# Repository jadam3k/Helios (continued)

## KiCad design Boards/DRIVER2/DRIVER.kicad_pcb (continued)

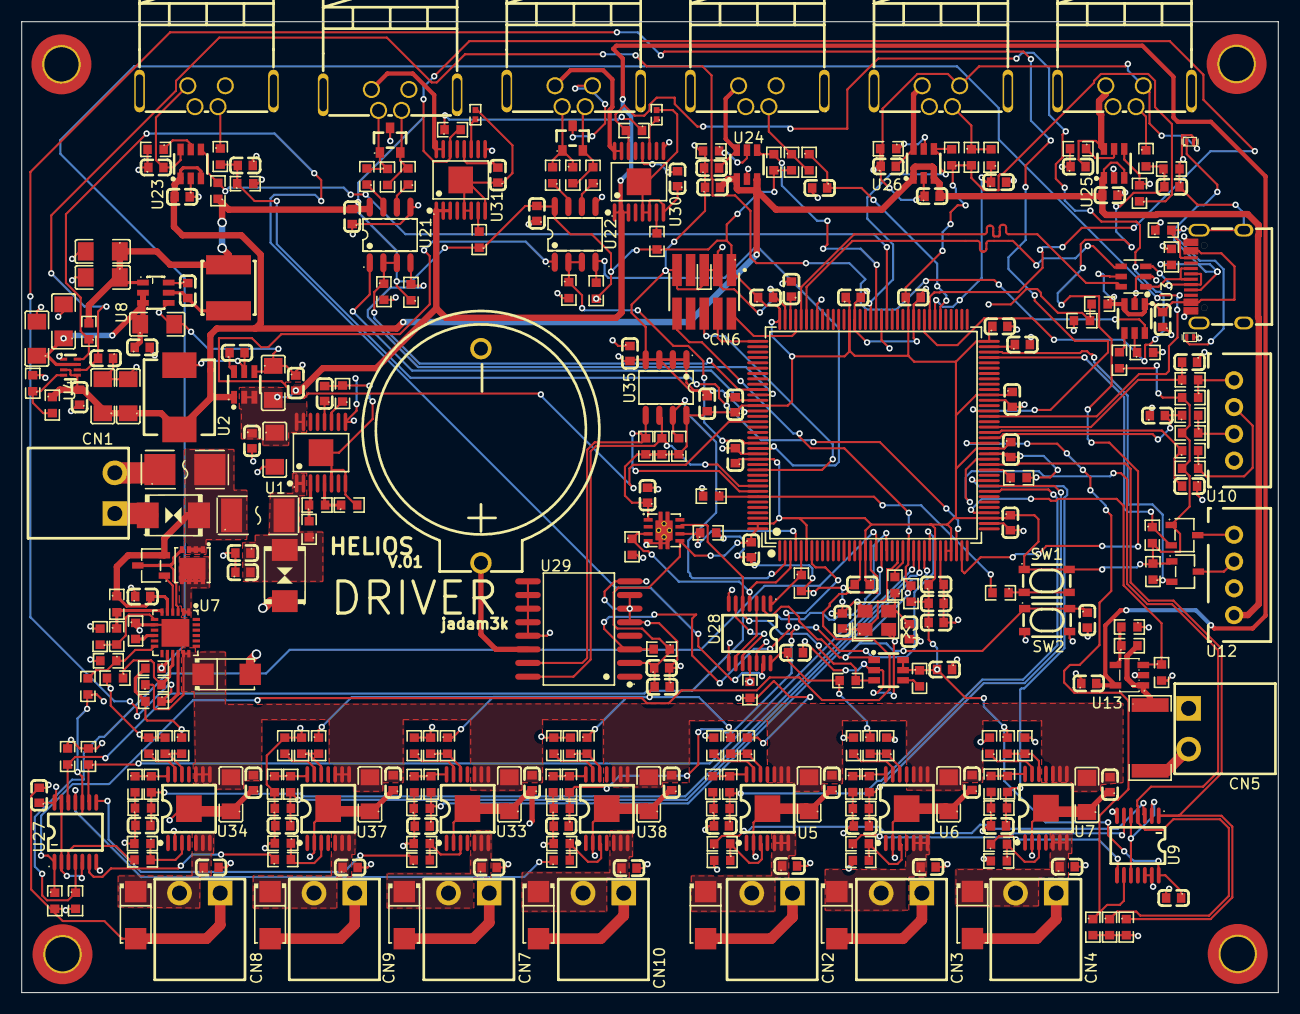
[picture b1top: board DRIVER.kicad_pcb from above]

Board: 4 copper layers, 117.3 x 90.6 mm, 322 parts (0 on the bottom side), 183 nets.

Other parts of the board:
M13, M13#2, M13#3, M13#4: MountingHole_3.2mm_M3_DIN965_Pad_TopBottom

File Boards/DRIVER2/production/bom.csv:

Designator,Footprint,Quantity,Value,LCSC Part #
BT1,C2895401_BAT-TH_BS-2-1,1,BS-2-1,C2895401
"C1, C11, C23, C25, C39, C62, C63, C70, C71, C82, C88",C15849_C0603,11,1uF,C15849
"C10, C12, C13, C2, C20, C24, C27, C31, C33, C34, C36, C37, C38, C40, C41, C42, C43, C44, C45, C46, C47, C48, C5, C53, C55, C57, C58, C59, C60, C65, C66, C67, C68, C69, C72, C73, C74, C75, C76, C79, C8, C80, C81, C87, C89, C9, C92, C93",C14663_C0603,48,100nF,C14663
"C14, C15, C21, C22, C32, C35, C83, C84, C85, C86, C94, C95, C96, C97",C1589_C0603,14,10nF,C1589
"C16, C17, C18, C19, C28, C29",C12891_C1206,6,22uF,C12891
"C26, C3, C30, C4, C6, C7, C77, C78, C90, C91",C13585_C1206,10,10uF,C13585
"C49, C51, C52, C61",C57112_C0603,4,10nF,C57112
"C50, C54",C1607_C0603,2,2.2uF,C1607
"C56, C64",C1647_C0603,2,18pF,C1647
CN1,C507005_CONN-TH_2P-P3_81_JL15EDGRC-38102G01,1,15EDGRC-3.81-02P,C507005
"CN10, CN2, CN3, CN4, CN5, CN7, CN8, CN9",C507005_CONN-TH_2P-P3_81_JL15EDGRC-38102G01,8,15EDGRC-3.81-02P-14-00A(H),C507005
CN6,C448647_CONN-SMD_FTSH-105-01-L-DV-K-TR,1,FTSH-105-01-L-DV-K-TR,C448647
"D1, D2",C83327_SMB_L4_6-W3_6-LS5_3-BI,2,SMBJ18CA,C83327
"D10, D11, D12, D13, D3, D4, D5, D7",C65009_SMA_L4_3-W2_6-LS5_2-RD,8,SS56,C65009
D6,C7519_SOT-23-6_L2_9-W1_6-P0_95-LS2_8-BL,1,USBLC6-2SC6,C7519
"D8, D9",C404012_SOT-23_L2_9-W1_3-P1_90-LS2_4-BR,2,CDSOT23-SM712,C404012
"E1, E2",C84374_SOD-882_L1_0-W0_6-BI,2,14V,C84374
F1,C178980_FUSE-SMD_L6_1-W2_7,1,"8A,65V",C178980
F2,C99547_FUSE-SMD_L6_1-W2_7_0451002_MRL,1,2 A / 0451002.MRL.,C99547
L1,C3040353_IND-SMD_L7_0-W6_6,1,FAUL0630,C3040353
L2,C167962_IND-SMD_L5_0-W5_0_FNR50XXS,1,FNR5040S3R9NT,C167962
Q1,C478469_DFN-8_L3_3-W3_3-P0_65-BL-3,1,CSD19537Q3,C478469
"Q2, Q3, Q4",C40912_SOT-23-3_L2_9-W1_6-P1_90-LS2_8-BR,3,BSS138-7-F,C40912
"R1, R106, R107, R110, R111, R126, R127, R129, R130, R134, R135, R2, R3, R36, R37, R4, R46, R51, R52, R55, R61, R73, R82",C23162_R0603,23,4.7k,C23162
"R10, R102, R103, R104, R105, R117, R119, R12, R120, R121, R122, R123, R128, R140, R141, R142, R143, R15, R17, R18, R19, R25, R27, R28, R33, R41, R42, R48, R49, R50, R57, R59, R62, R63, R64, R65, R66, R74, R75, R80, R81, R83, R84, R86, R87, R89, R90, R95, R96, R97, R98, R99",C25804_R0603,52,10k,C25804
"R100, R101, R23, R93, R94",C25808_R0603,5,120k,C25808
"R108, R109, R11, R112, R113, R131, R132, R133, R136, R137, R34, R35, R38, R39, R5, R6, R7, R8",C25803_R0603,18,100k,C25803
"R114, R116",C2986234_R0402,2,60.4k,C2986234
"R115, R118, R13, R138, R139, R14, R40",C23179_R0603,7,470R,C23179
"R124, R125, R144, R145, R20, R21, R43",C23253_R0603,7,820R,C23253
R16,C22790_R0603,1,12k,C22790
R22,C23231_R0603,1,68k,C23231
R24,C25981_R0603,1,8.2k,C25981
R26,C23040_R0603,1,"4.02 kΩ, ±1%",C23040
"R29, R32",C23240_R0603,2,750k,C23240
R30,C54531393_R0603,1,34.8k,C54531393
R31,C14891_R0603,1,64.9k,C14891
"R44, R45",C23186_R0603,2,5.1k,C23186
"R47, R53, R54, R76, R85, R88",C21190_R0603,6,1KΩ,C21190
R56,C22935_R0603,1,1M,C22935
R58,C31850_R0603,1,22k,C31850
R60,C35218_R2512,1,100R,C35218
R67,C4216_R0603,1,33k,C4216
R68,C23254_R0603,1,82k,C23254
"R69, R70, R71, R72",C313648_R0603,4,10R,C313648
"R77, R78",C22809_R0603,2,15k,C22809
R79,C21189_R0603,1,0R0,C21189
R9,C22984_R0603,1,30k,C22984
"R91, R92",C22787_R0603,2,120R,C22787
"SW1, SW2",C139797_KEY-SMD_4P-L4_2-W3_2-P2_20-LS4_6,2,SKRPACE010,C139797
"U1, U30, U31",C544399_HTSSOP-16_L5_0-W4_4-P0_65-LS6_4-BL-EP2_5,3,TPS26600PWPR,C544399
"U10, U12",C144395_CONN-TH_B4B-XH-A-LF-SN,2,B4B-XH-A(LF)(SN),C144395
"U11, U33, U34, U37, U38, U5, U6",C475505_PDSO-G14_L5_0-W4_4-P0_65-LS6_4-BL-EP,7,TPS1H100BQPWPRQ1,C475505
U13,C221351_SOT-23-5_L3_0-W1_7-P0_95-LS2_8-BR,1,OPA197IDBVR,C221351
U14,C46525_LQFP-144_L20_0-W20_0-P0_50-LS22_0-BL,1,STM32F429ZGT6,C46525
"U15, U16, U17, U18, U19, U20",C19108970_SMA-TH_M8-S4A-GPL-M10-JD,6,M8-S4A-GPL M10-JD,C19108970
U2,C2071056_TSOT-23-6_L2_9-W1_6-P0_95-LS2_8-BL,1,AP63205WU-7,C2071056
"U21, U22",C2671345_SOIC-8_L4_9-W3_9-P1_27-LS6_0-BL,2,THVD1410DR,C2671345
"U23, U24, U25, U26, U3",C55266_SOT-23-6_L2_9-W1_6-P0_95-LS2_8-BR,5,TPS2553DBVR,C55266
"U27, U28, U9",C2867158_TSSOP-14_L4_9-W4_4-P0_65-LS6_4-BL,3,SN74HCS08QPWRQ1,C2867158
U29,C9866_SOIC-16_L10_3-W7_5-P1_27-LS10_3-BL,1,DS3231,C9866
U32,C702145_VSON-8_L3_0-W3_0-P0_65-TL-EP,1,TPS3431SDRBR,C702145
U35,C66020_SOIC-8_L4_9-W3_9-P1_27-LS6_0-BL,1,FM24W256-GTR,C66020
U36,C43698_SOT-23-6_L2_9-W1_6-P0_95-LS2_8-BR,1,TPS3808G33DBVR,C43698
U4,C3235557_SOT-583-8_L2_1-W1_6-P0_50-LS1_6-BL,1,TPS2116DRLR,C3235557
U7,C1850273_VQFN-24_L4_0-W4_0-P0_50-BL-EP2_5,1,TPS26631RGER,C1850273
U8,C780769_TSOT-26_L2_9-W1_6-P0_95-LS2_8-BL,1,AP63203WU-7,C780769
USBC1,C165948_USB-C_SMD-TYPE-C-31-M-12_1,1,TYPE-C-31-M-12,C165948
X1,C2682775_CRYSTAL-SMD_4P-L3_2-W2_5-BL,1,X32258MOB4SI,C2682775

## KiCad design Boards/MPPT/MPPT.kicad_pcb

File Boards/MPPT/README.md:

# Helios MPPT

Solar power board for the Helios greenhouse controller, using an STM32L072CZT6. The original schematic and PCB are preserved. The 8P8C connector is not used by the firmware.

[PCB view](media/helios-mppt-pcb.png) · [Board video](media/helios-mppt-preview.mp4) · [Schematic](docs/MPPT.pdf) · [STEP](docs/MPPT.step) · [Interactive BOM](bom/ibom.html)

## Current firmware

The complete firmware now includes actual power-stage PWM, voltage/current/temperature measurements, current and voltage limiting, output-power perturb-and-observe, Li-ion charge termination/restart, load hysteresis, latched faults, a control heartbeat and watchdog.

[Open the Arduino sketch](firmware/HeliosMPPT/HeliosMPPT.ino) · [All source files in one text source text](firmware/COMPLETE_SOURCE.txt) · [Full firmware ZIP](firmware/HeliosMPPT-full.zip) · [Setup and calibration](firmware/README.md) · [Build results](firmware/BUILD_RESULTS.txt)

Compiled successfully for Generic L072CZTx with STM32 Arduino core 3.1.0, in both the default and confirmed charging configurations, with no compiler warnings. Host tests passed 25 checks and exercised 88 duty settings in both timer directions. The assembled board and charger still need bench testing.

**Battery/calibration confirmation defaults to off.** After confirming a protected 3S Li-ion battery and calibrating sensors, set HELIOS_BATTERY_CONFIRMED and HELIOS_CALIBRATION_CONFIRMED to 1 in Config.h. The implemented charger then starts automatically after valid solar qualification. This is a 12.55 V / 2 A reference profile; it is not for AGM or 4S LiFePO4. TH1 beta remains an explicit calibration input.

The original AP2210 and LM5109B supply operating limits remain relevant. A 14.5 V AGM profile is not supported by the unchanged design. Default diode freewheeling raises low-side losses; the optional synchronous mode and actual MOSFET waveforms require bench checks. See the firmware instructions for the controls and limits.

## Hardware

| Block | Components | Purpose |
| --- | --- | --- |
| MCU | STM32L072CZTx, LQFP48 | ADC, DAC, GPIO and timer control; supported by the STM32 Arduino core |
| Converter | Q3–Q5 PSMN5R2-60YL, LM5109BMA, L1 CPEX3222L-470MC-RS | Solar input switching and synchronous buck stage |
| Current sensing | INA2181A1, two 3 mΩ shunts | Converter output current and load current; nominal sensitivity 60 mV/A |
| Voltage sensing | 100 kΩ / 5.6 kΩ dividers | Battery and solar voltage; divider ratio 18.857 |
| Temperature | TH1 10 kΩ NTC | Temperature input; its beta value is not specified in the design |
| Load switch | BSC084P03NS3 G, MMBT3904 | MCU-controlled battery/load output |
| Auxiliary power | LMR33630, AP2210K-3.3 | 5 V buck and 3.3 V LDO |
| Connections | Three screw terminals, XT30, two USB-A sockets, SWD | Power, loads and programming |

The XT30 output is on the unswitched load rail. Turning off LOAD_EN does not disconnect it or the 5 V buck. F2 is a fuse holder: the fitted fuse must be specified separately. Component headline current ratings do not establish the assembled board's continuous current rating.

## Connector and firmware pin map

| Connection | MCU / connector assignment |
| --- | --- |
| Solar U1 | Pin 2 SOLAR+, pin 1 SOLAR−; use the labeled input return |
| Battery U6 | Pin 1 BAT+, pin 2 GND |
| Switched load U5 | Pin 1 switched positive, pin 2 GND |
| XT30 U4 | Pin 1 LOAD_SOLAR, pin 2 GND |
| SWD J4 | 1 VTref 3.3 V, 2 SWCLK, 3 GND, 4 SWDIO, 5 NRST |
| Battery / panel voltage | PA0 / PA1 |
| Current reference DAC | PA4; approximately half VDDA |
| Load / converter current | PA5 / PA6 |
| NTC measurement / return | PA7 / PA8 |
| Driver HI / LI | PB0 / PB1; TIM3 CH3/CH4 PWM, LOW while stopped or unconfigured |
| Switched load enable | PC13; active-HIGH switched load with voltage hysteresis and fault shutdown |
| PV measurement enable | PC14; HIGH enables the divider, not the power converter |
| 5 V status | PC15; Q8 makes LOW mean power-good |
| 5 V buck enable | PB10 |

## Getting started

Open the Arduino sketch using [these firmware instructions](firmware/README.md). For the connections between both boards and the first hardware checks, see [system setup](../../docs/SETUP.md). The defaults leave charging off until the battery and calibration settings are confirmed.

## Project files

| Path | Contents |
| --- | --- |
| `MPPT.kicad_pro`, `.kicad_sch`, `.kicad_pcb` | Original KiCad project and source files |
| `libs/`, `fp-lib-table`, `sym-lib-table` | Required local symbols, footprints and models |
| `firmware/HeliosMPPT/` | Complete Arduino sketch, configuration, controller and PWM driver |
| `firmware/tests/` | Host C++ controller tests |
| `docs/` | Schematic PDF and STEP model |
| `media/` | Render, PCB image and original video |
| `MPPT.glb` | Interactive 3D model, kept beside the KiCad project export settings |
| `production/` | Existing manufacturing exports, preserved unchanged |
| `bom/` | Interactive BOM and a source-derived parts list with available links |

## Bill of materials

[Original manufacturing BOM](production/bom.csv) · [Expanded parts list](bom/parts-with-links.csv) · [Combined system BOM](../../BOM.csv)

The table describes the original board. Parts without an assigned supplier number still need an exact manufacturer part to be selected, including the necessary voltage, power and package ratings.

The tables use direct supplier product links. Prices are USD per component at the stated quantity tier, checked on **November 19, 2026**. Costs use the required component quantities; the final cart can cost more because of minimum order quantities. Shipping, tax, fabrication and assembly are separate.

| References | Qty | Board value | Manufacturer part | Supplier | USD/part | Price tier |
| --- | ---: | --- | --- | --- | ---: | ---: |
| C1 | 1 | 10nF | — | Not selected | — | — |
| C2, C21, C36 | 3 | 2.2uF | — | Not selected | — | — |
| C3, C6, C8, C26, C27, C28, C29, C30, C31, C34 | 10 | 100nF | — | Not selected | — | — |
| C4 | 1 | 1200uF | — | Not selected | — | — |
| C5, C10, C12, C15, C16, C17, C18, C20, C23, C38 | 10 | 10nF | — | Not selected | — | — |
| C7 | 1 | 4.7uF | — | Not selected | — | — |
| C9, C11, C13 | 3 | 1nF | — | Not selected | — | — |
| C14 | 1 | 820uF | — | Not selected | — | — |
| C19 | 1 | 1uF | — | Not selected | — | — |
| C22 | 1 | 150uF | — | Not selected | — | — |
| C24 | 1 | 10uF | — | Not selected | — | — |
| C25 | 1 | 220nF | — | Not selected | — | — |
| C32, C41 | 2 | 2.2uF | — | Not selected | — | — |
| C33, C35, C37, C39 | 4 | 22uF | — | Not selected | — | — |
| C40 | 1 | 100pF | — | Not selected | — | — |
| D1, D2, D5 | 3 | 1N4148W | — | Not selected | — | — |
| D3 | 1 | SS14 | — | Not selected | — | — |
| D4 | 1 | SMBJ24A_C123819 | SMBJ24A | [C123819](https://www.lcsc.com/product-detail/C123819.html) | 0.0593 | 10 |
| F2 | 1 | 3557-2 | 3557-2 | [C352820](https://www.lcsc.com/product-detail/C352820.html) | 1.4802 | 1 |
| J4 | 1 | Conn_01x05 | — | Not selected | — | — |
| L1 | 1 | CPEX3222L-470MC-RS | CPEX3222L-470MC-RS | [C53145486](https://www.lcsc.com/product-detail/C53145486.html) | 5.0594 | 1 |
| L2 | 1 | 2.2uH | — | Not selected | — | — |
| L3 | 1 | SRN8040TA | SRN8040TA-100M | [C2044906](https://www.lcsc.com/product-detail/C2044906.html) | 0.7615 | 1 |
| Q2, Q8, Q9 | 3 | BSS83P | — | Not selected | — | — |
| Q3, Q4, Q5 | 3 | PSMN5R2-60YL | — | Not selected | — | — |
| Q6, Q7 | 2 | MMBT3904 | — | Not selected | — | — |
| Q10 | 1 | BSC084P03NS3 G | BSC084P03NS3GATMA1 | [C672354](https://www.lcsc.com/product-detail/C672354.html) | 1.1136 | 1 |
| R1, R17, R18, R25 | 4 | 10k | — | Not selected | — | — |
| R2, R24 | 2 | 24.9k | — | Not selected | — | — |
| R3, R4, R10, R21, R22, R23, R30 | 7 | 100k | — | Not selected | — | — |
| R5, R11 | 2 | 5.6k | — | Not selected | — | — |
| R6 | 1 | 1M | — | Not selected | — | — |
| R7, R9, R27, R29 | 4 | 470 | — | Not selected | — | — |
| R8, R13 | 2 | 4R7 | — | Not selected | — | — |
| R12 | 1 | 4R7 | — | Not selected | — | — |
| R14, R19 | 2 | 3mR | CRE2512-FZ-R001E-3 | [C840615](https://www.lcsc.com/product-detail/C840615.html) | 0.4295 | 1 |
| R15, R26, R28, R31 | 4 | 2.2k | — | Not selected | — | — |
| R16 | 1 | 2R2 | — | Not selected | — | — |
| R20 | 1 | 100 | — | Not selected | — | — |
| RJ1 | 1 | HX-RJ45 90 5631-1X1 8P8C S | HX-RJ45 90 5631-1x1 8P8C S | [C25168872](https://www.lcsc.com/product-detail/C25168872.html) | 0.1430 | 5 |
| TH1 | 1 | 10K NTC | — | Not selected | — | — |
| TP1 | 1 | PWM_HS_TP | — | Not selected | — | — |
| TP2 | 1 | PWM_LS_TP | — | Not selected | — | — |
| TP3 | 1 | REF_TP | — | Not selected | — | — |
| TP4 | 1 | DCDC_CURRENT_TP | — | Not selected | — | — |
| TP5 | 1 | LOAD_CURRENT_TP | — | Not selected | — | — |
| TP6 | 1 | 12VTP | — | Not selected | — | — |
| TP7 | 1 | 5V_TP | — | Not selected | — | — |
| TP8 | 1 | 3.3V_TP | — | Not selected | — | — |
| U1, U5, U6 | 3 | KF135T-10.16-2P | KF135T-10.16-2P | [C475108](https://www.lcsc.com/product-detail/C475108.html) | 0.5699 | 1 |
| U2 | 1 | INA2181A | INA2181A1IDGSR | [C1848164](https://www.lcsc.com/product-detail/C1848164.html) | 0.5701 | 1 |
| U3 | 1 | LM5109BMA | LM5109BMA/NOPB | [C1549317](https://www.lcsc.com/product-detail/C1549317.html) | 1.0736 | 1 |
| U4 | 1 | XT30AW-M.G.Y | XT30AW-M.G.Y | [C19268026](https://www.lcsc.com/product-detail/C19268026.html) | 0.4097 | 1 |
| U7 | 1 | STM32L072CZTx | STM32L072CZT6 | [C1337587](https://www.lcsc.com/product-detail/C1337587.html) | 5.9667 | 1 |
| U8 | 1 | LMR33630 | LMR33630ADDA | [C2866787](https://www.lcsc.com/product-detail/C2866787.html) | 1.0284 | 1 |
| U9 | 1 | AP2210K-3.3TRG1 | AP2210K-3.3TRG1 | [C176959](https://www.lcsc.com/product-detail/C176959.html) | 0.1626 | 5 |
| USB1, USB2 | 2 | USB-231-ARY | USB-231-ARY | [C720525](https://www.lcsc.com/product-detail/C720525.html) | 0.1971 | 5 |

U3, U7 and U8 use catalog references added to the documentation; they do not change the schematic or manufacturing files. Codes recovered from footprint names still need a part/package check before an order.

## Development and reuse

This is part of my Helios greenhouse project. See [development credits](../../CREDITS.md) for assistance and third-party dependencies. A project-wide license has not been selected.

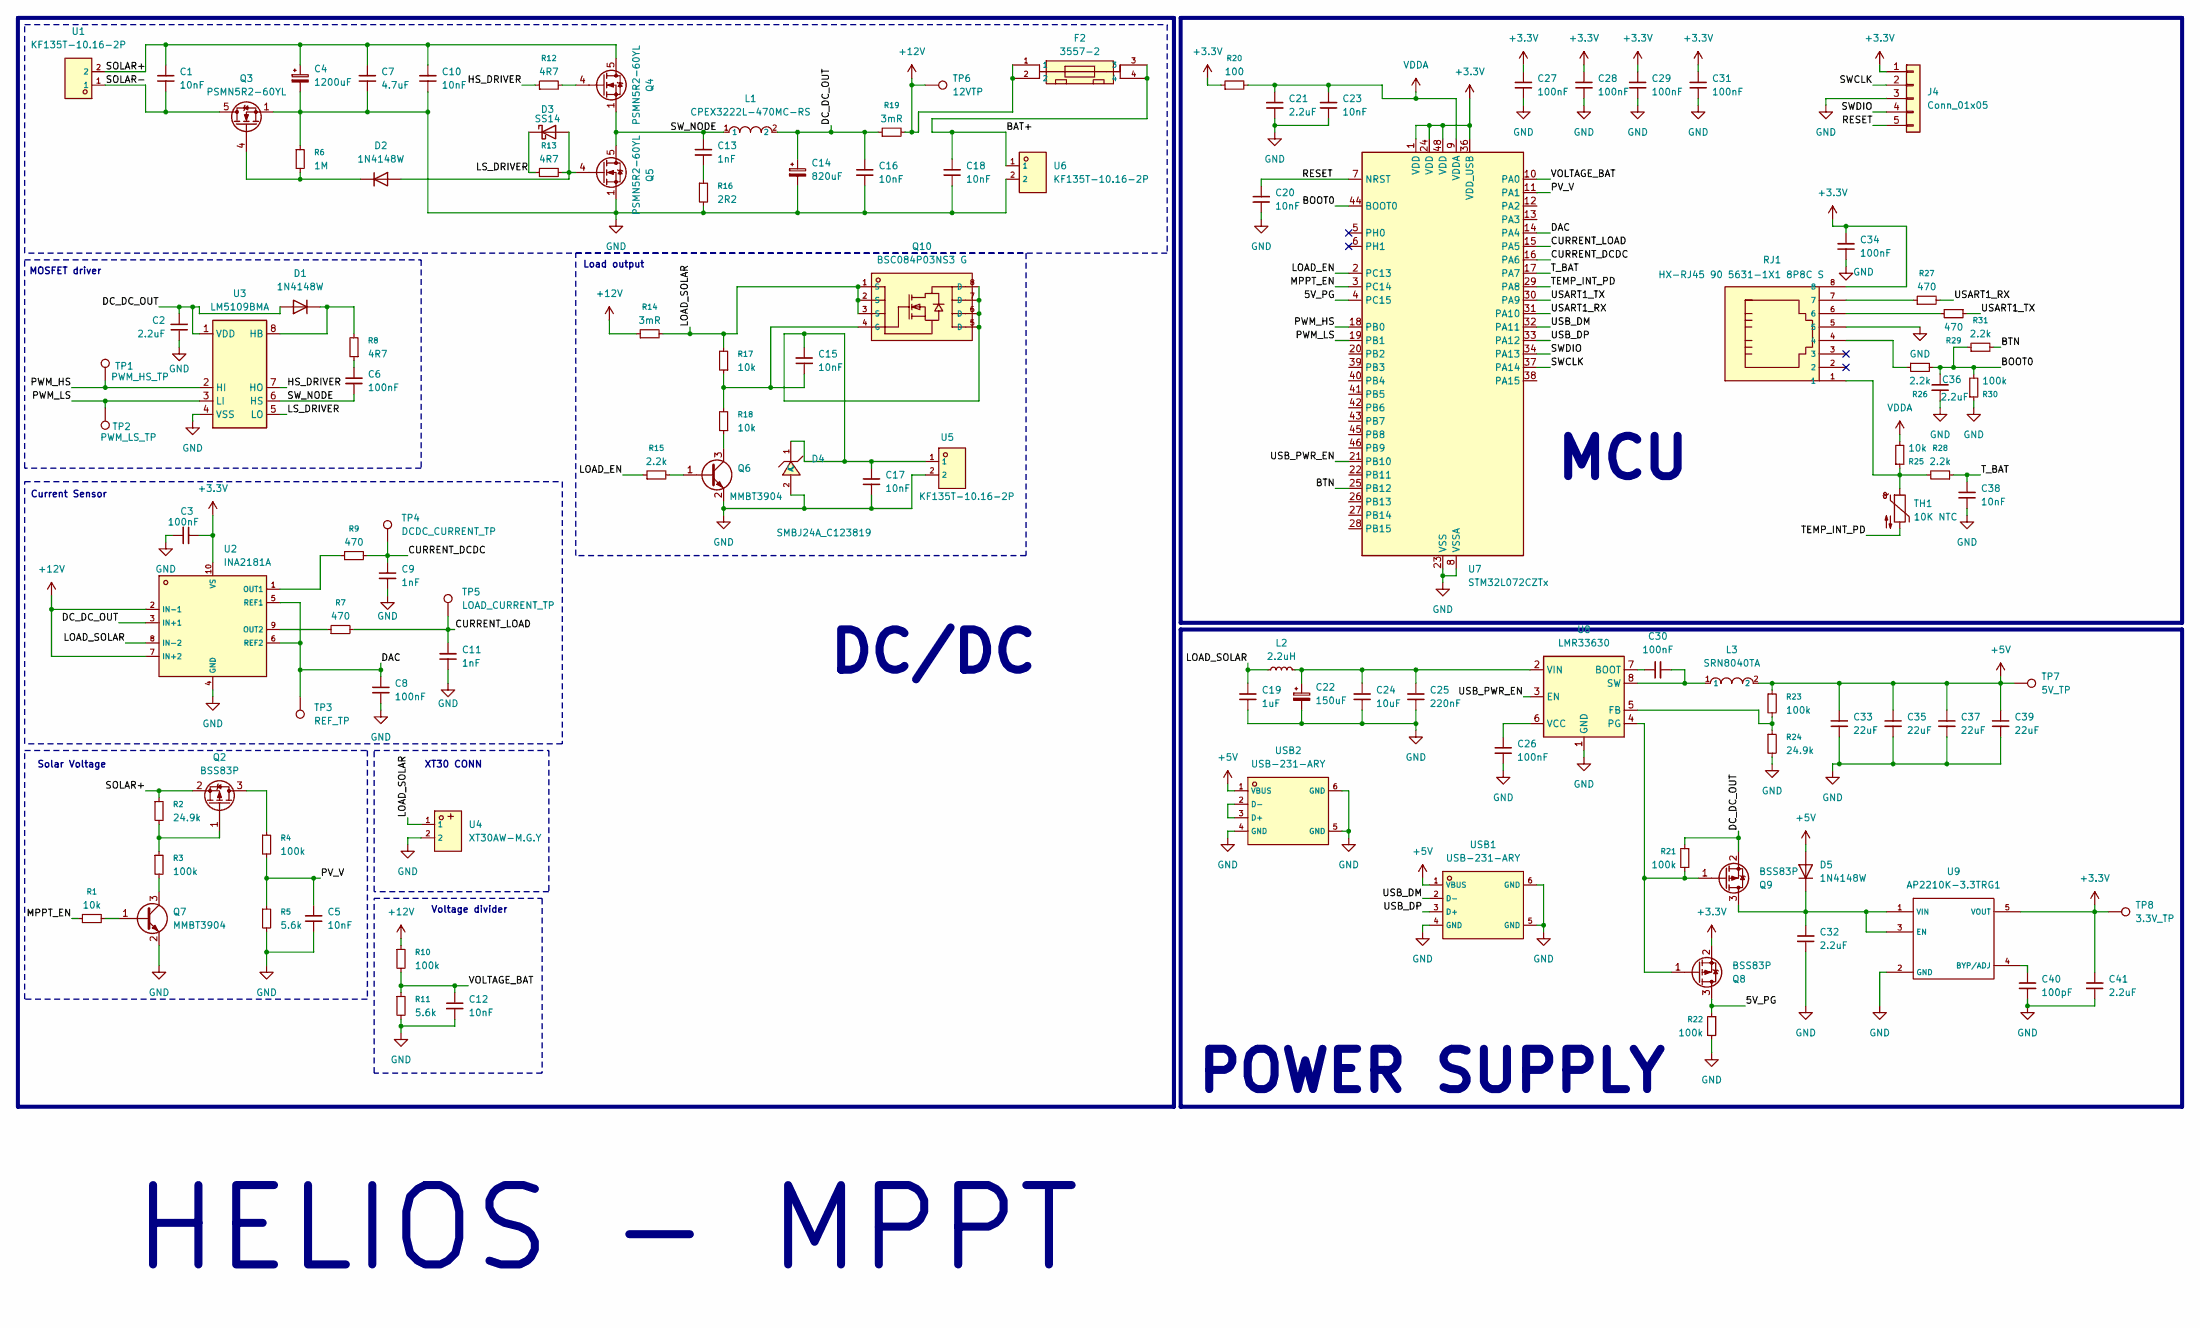
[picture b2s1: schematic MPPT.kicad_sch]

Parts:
C1: 10nF; C_1206_3216Metric
C2, C21, C36: 2.2uF; C_0603_1608Metric
C3, C6, C8, C26, C27, C28, C29, C30, C31, C34: 100nF; C_0603_1608Metric
C4: 1200uF; CP_Radial_D16.0mm_P7.50mm
C5, C10, C12, C15, C16, C17, C18, C20, C23, C38: 10nF; C_0603_1608Metric
C7: 4.7uF; C_1206_3216Metric
C9, C11, C13: 1nF; C_0603_1608Metric
C14: 820uF; CP_Radial_D10.0mm_P5.00mm
C19: 1uF; C_0805_2012Metric
C22: 150uF; CP_Elec_8x6.2
C24: 10uF; C_1210_3225Metric
C25: 220nF; C_0603_1608Metric
C32, C41: 2.2uF; C_1206_3216Metric
C33, C35, C37, C39: 22uF; C_1206_3216Metric
C40: 100pF; C_0603_1608Metric
D1, D2, D5: 1N4148W; D_SOD-123
D3: SS14; D_SMA
D4: SMBJ24A_C123819; C123819_SMB_L4_6-W3_6-LS5_3-RD; LCSC C123819
F2: 3557-2; C352820_FUSE-TH_4P-L19_8-W6_7_3557-2; LCSC C352820
J4: Conn_01x05; PinHeader_1x05_P2.54mm_Vertical
L1: CPEX3222L-470MC-RS; C53145486_IND-TH_L32_2-W22_2_CPEX3222L; LCSC C53145486
L2: 2.2uH; L_Bourns-SRN4018
L3: SRN8040TA; C2044906_IND-SMD_L8_0-W8_0; LCSC C2044906
Q2, Q8, Q9: BSS83P; SOT-23
Q3, Q4, Q5: PSMN5R2-60YL; LFPAK56
Q6, Q7: MMBT3904; SOT-23
Q10: BSC084P03NS3 G; C534379_TDSON-8_L5_2-W5_9-P1_27-LS6_0-BL-EP; LCSC C534379
R1, R17, R18, R25: 10k; R_0603_1608Metric
R2, R24: 24.9k; R_0603_1608Metric
R3, R4, R10, R21, R22, R23, R30: 100k; R_0603_1608Metric
R5, R11: 5.6k; R_0603_1608Metric
R6: 1M; R_0603_1608Metric
R7, R9, R27, R29: 470; R_0603_1608Metric
R8, R13: 4R7; R_0603_1608Metric
R12: 4R7; R_0805_2012Metric
R14, R19: 3mR; C840615_R2512
R15, R26, R28, R31: 2.2k; R_0603_1608Metric
R16: 2R2; R_0603_1608Metric
R20: 100; R_0603_1608Metric
RJ1: HX-RJ45 90 5631-1X1 8P8C S; C25168872_RJ45-TH_HX-RJ45-90; LCSC C25168872
TH1: 10K NTC; R_Axial_DIN0204_L3.6mm_D1.6mm_P5.08mm_Horizontal
TP1: PWM_HS_TP; TestPoint_Pad_D1.0mm
TP2: PWM_LS_TP; TestPoint_Pad_D1.0mm
TP3: REF_TP; TestPoint_Pad_D1.0mm
TP4: DCDC_CURRENT_TP; TestPoint_Pad_D1.0mm
TP5: LOAD_CURRENT_TP; TestPoint_Pad_D1.0mm
TP6: 12VTP; TestPoint_Pad_D1.0mm
TP7: 5V_TP; TestPoint_Pad_D1.0mm
TP8: 3.3V_TP; TestPoint_Pad_D1.0mm
U1, U5, U6: KF135T-10.16-2P; C475108_CONN-TH_P10_16_KF135T-10_16-2P; LCSC C475108
U2: INA2181A; C1848164_VSSOP-10_L3_0-W3_0-P0_50-LS4_9-BL; LCSC C1848164
U3: LM5109BMA; SOIC-8_3.9x4.9mm_P1.27mm
U4: XT30AW-M.G.Y; C19268026_CONN-TH_XT30AW-M_G_Y; LCSC C19268026
U7: STM32L072CZTx; LQFP-48_7x7mm_P0.5mm
U8: LMR33630; Texas_HSOP-8-1EP_3.9x4.9mm_P1.27mm_ThermalVias
U9: AP2210K-3.3TRG1; C176959_SOT-23-5_L3_0-W1_7-P0_95-LS2_8-BR; LCSC C176959
USB1, USB2: USB-231-ARY; C720525_USB-A-TH_USB-231-ARY; LCSC C720525

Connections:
+3.3V: C3.2, C27.1, C28.1, C29.1, C31.1, C34.1, C41.1, J4.1, Q8.2 (S), R20.1, RJ1.8, TP8.1 (1_1), U2.10 (VS), U7.1 (VDD), U7.24 (VDD), U7.36 (VDD_USB), U7.48 (VDD), U9.5 (VOUT)
+5V: C33.1, C35.1, C37.1, C39.1, D5.2 (A), L3.2, R23.1, TP7.1 (1_1), USB1.1 (VBUS), USB2.1 (VBUS)
+12V: F2.1, F2.2, R10.1, R14.1, R19.2, TP6.1 (1_1), U2.2 (IN-1), U2.7 (IN+2)
/5V_PG: Q8.3 (D), R22.1, U7.4 (PC15)
/BAT+: C18.1, F2.3, F2.4, U6.1
/BOOT0: C36.1, R26.2, R30.2, R31.1, U7.44 (BOOT0)
/BTN: R31.2, U7.25 (PB12)
/CURRENT_DCDC: C9.1, R9.2, TP4.1 (1_1), U7.16 (PA6)
/CURRENT_LOAD: C11.1, R7.2, TP5.1 (1_1), U7.15 (PA5)
/DAC: C8.1, TP3.1 (1_1), U2.5 (REF1), U2.6 (REF2), U7.14 (PA4)
/DC_DC_OUT: C2.1, C14.1, C16.1, D1.2 (A), L1.2, Q9.2 (S), R19.1, R21.1, U2.3 (IN+1), U3.1 (VDD)
/HS_DRIVER: R12.1, U3.7 (HO)
/LOAD_EN: R15.1, U7.2 (PC13)
/LOAD_SOLAR: C19.1, L2.1, Q10.1 (S), Q10.2 (S), Q10.3 (S), R14.2, R17.2, U2.8 (IN-2), U4.1
/LS_DRIVER: D3.1 (K), R13.1, U3.5 (LO)
/MPPT_EN: R1.1, U7.3 (PC14)
/PV_V: C5.1, R4.2, R5.1, U7.11 (PA1)
/PWM_HS: TP1.1 (1_1), U3.2 (HI), U7.18 (PB0)
/PWM_LS: TP2.1 (1_1), U3.3 (LI), U7.19 (PB1)
/RESET: C20.1, J4.5, U7.7 (NRST)
/SOLAR+: C1.1, C4.1, C7.1, C10.1, Q2.2 (S), Q4.5 (D), R2.1, U1.2
/SOLAR-: C1.2, Q3.5 (D), U1.1
/SWCLK: J4.2, U7.37 (PA14)
/SWDIO: J4.4, U7.34 (PA13)
/SW_NODE: C6.2, C13.1, L1.1, Q4.1 (S), Q4.2 (S), Q4.3 (S), Q5.5 (D), U3.6 (HS)
/TEMP_INT_PD: TH1.2, U7.29 (PA8)
/T_BAT: C38.1, R28.1, U7.17 (PA7)
/USART1_RX: R27.2, U7.31 (PA10)
/USART1_TX: R29.1, U7.30 (PA9)
/USB_DM: U7.32 (PA11), USB1.2 (D-)
/USB_DP: U7.33 (PA12), USB1.3 (D+)
/USB_PWR_EN: U7.21 (PB10), U8.3 (EN)
/VOLTAGE_BAT: C12.1, R10.2, R11.1, U7.10 (PA0)
GND: C2.2, C3.1, C4.2, C5.2, C7.2, C8.2, C9.2, C10.2, C11.2, C12.2, C14.2, C16.2, C17.2, C18.2, C19.2, C20.2, C21.2, C22.2, C23.2, C24.2, C25.2, C26.2, C27.2, C28.2, C29.2, C31.2, C32.2, C33.2, C34.2, C35.2, C36.2, C37.2, C38.2, C39.2, C40.2, C41.2, D4.2 (A), J4.3, Q3.1 (S), Q3.2 (S), Q3.3 (S), Q5.1 (S), Q5.2 (S), Q5.3 (S), Q6.2 (E), Q7.2 (E), R5.2, R6.1, R11.2, R16.2, R22.2, R24.2, R30.1, RJ1.5, U2.4 (GND), U3.4 (VSS), U4.2, U5.2, U6.2, U7.8 (VSSA), U7.23 (VSS), U7.35 (VSS), U7.47 (VSS), U8.1 (GND), U8.9 (GND), U9.2 (GND), USB1.4 (GND), USB1.5 (GND), USB1.6 (GND), USB2.4 (GND), USB2.5 (GND), USB2.6 (GND)
unnamed: C6.1, R8.1
unnamed: C13.2, R16.1
unnamed: D1.1 (K), R8.2, U3.8 (HB)
unnamed: D2.2 (A), D3.2 (A), Q5.4 (G), R13.2
unnamed: D2.1 (K), Q3.4 (G), R6.2
unnamed: C15.1, C17.1, D4.1 (C), Q10.5 (D), Q10.6 (D), Q10.7 (D), Q10.8 (D), U5.1
unnamed: C32.1, D5.1 (K), Q9.3 (D), U9.1 (VIN), U9.3 (EN)
unnamed: Q2.3 (D), R4.1
unnamed: Q2.1 (G), R2.2, R3.1
unnamed: Q4.4 (G), R12.2
unnamed: Q6.1 (B), R15.2
unnamed: Q6.3 (C), R18.1
unnamed: Q7.1 (B), R1.2
unnamed: Q7.3 (C), R3.2
unnamed: Q8.1 (G), Q9.1 (G), R21.2, U8.4 (PG)
unnamed: C15.2, Q10.4 (G), R17.1, R18.2
unnamed: R25.1, R28.2, RJ1.1, TH1.1
unnamed: R26.1, RJ1.4
unnamed: R27.1, RJ1.7
unnamed: R29.2, RJ1.6
unnamed: R9.1, U2.1 (OUT1)
unnamed: R7.1, U2.9 (OUT2)
unnamed: C30.1, U8.7 (BOOT)
unnamed: R23.2, R24.1, U8.5 (FB)
unnamed: C30.2, L3.1, U8.8 (SW)
unnamed: C26.1, U8.6 (VCC)
unnamed: C22.1, C24.1, C25.1, L2.2, U8.2 (VIN)
unnamed: C40.1, U9.4 (BYP/ADJ)
unnamed: USB2.2 (D-), USB2.3 (D+)
VDDA: C21.1, C23.1, R20.2, R25.2, U7.9 (VDDA)

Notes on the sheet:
XT30 CONN
POWER SUPPLY
MCU
MOSFET driver
HELIOS - MPPT
Load output
DC/DC
Current Sensor
Voltage divider
Solar Voltage

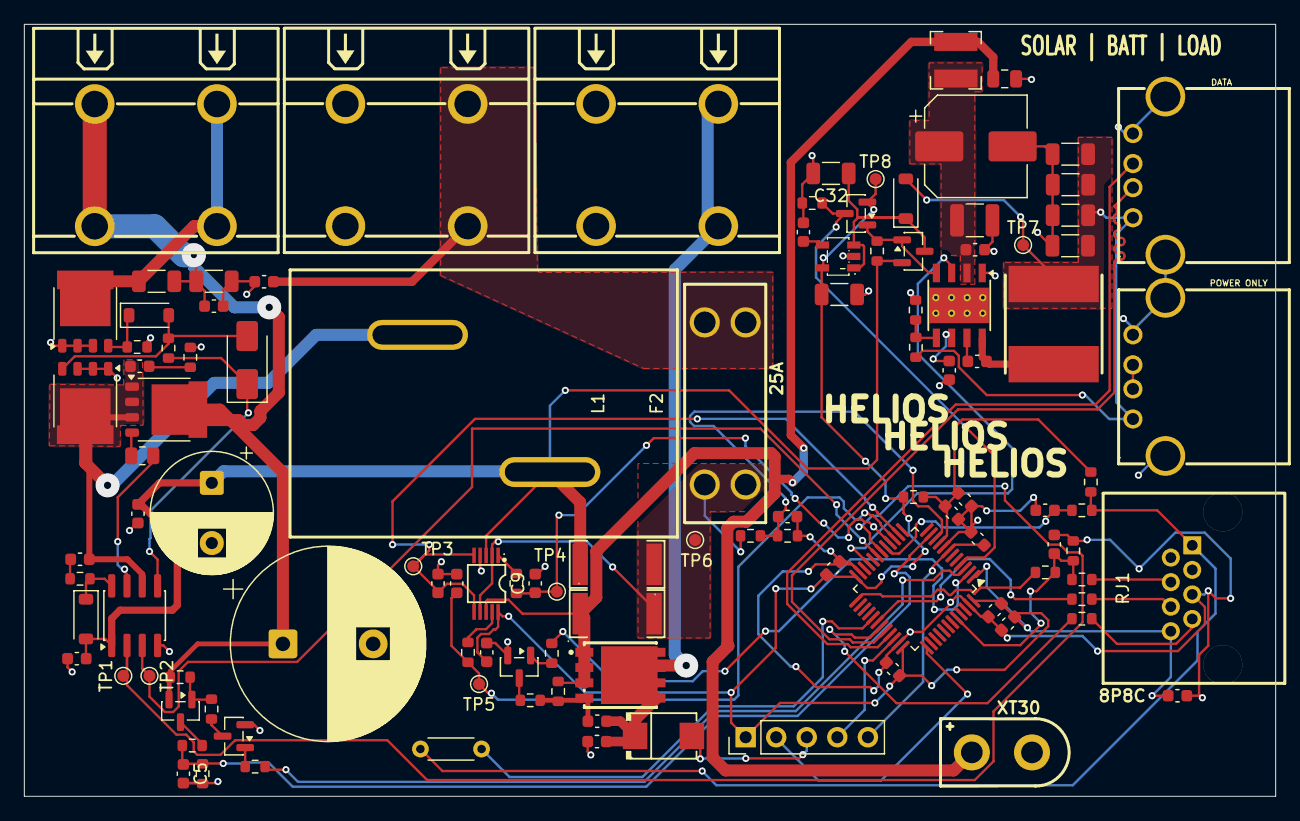
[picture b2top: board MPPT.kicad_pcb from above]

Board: 2 copper layers, 104.0 x 64.2 mm, 112 parts (0 on the bottom side), 64 nets.

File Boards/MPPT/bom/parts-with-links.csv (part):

"Board","Designators","Quantity","Value","Footprint","LCSC","Supplier URL","Unit USD","Line USD","Price date","Notes"
"MPPT","C1","1","10nF","Capacitor_SMD:C_1206_3216Metric","","","","n.a.","","Supplier part not selected"
"MPPT","C2, C21, C36","3","2.2uF","Capacitor_SMD:C_0603_1608Metric","","","","n.a.","","Supplier part not selected"
"MPPT","C3, C6, C8, C26, C27, C28, C29, C30, C31, C34","10","100nF","Capacitor_SMD:C_0603_1608Metric","","","","n.a.","","Supplier part not selected"
"MPPT","C4","1","1200uF","Capacitor_THT:CP_Radial_D16.0mm_P7.50mm","","","","n.a.","","Supplier part not selected"
"MPPT","C5, C10, C12, C15, C16, C17, C18, C20, C23, C38","10","10nF","Capacitor_SMD:C_0603_1608Metric","","","","n.a.","","Supplier part not selected"
"MPPT","C7","1","4.7uF","Capacitor_SMD:C_1206_3216Metric","","","","n.a.","","Supplier part not selected"
"MPPT","C9, C11, C13","3","1nF","Capacitor_SMD:C_0603_1608Metric","","","","n.a.","","Supplier part not selected"
"MPPT","C14","1","820uF","Capacitor_THT:CP_Radial_D10.0mm_P5.00mm","","","","n.a.","","Supplier part not selected"
"MPPT","C19","1","1uF","Capacitor_SMD:C_0805_2012Metric","","","","n.a.","","Supplier part not selected"
"MPPT","C22","1","150uF","Capacitor_SMD:CP_Elec_8x6.2","","","","n.a.","","Supplier part not selected"
"MPPT","C24","1","10uF","Capacitor_SMD:C_1210_3225Metric","","","","n.a.","","Supplier part not selected"
"MPPT","C25","1","220nF","Capacitor_SMD:C_0603_1608Metric","","","","n.a.","","Supplier part not selected"
"MPPT","C32, C41","2","2.2uF","Capacitor_SMD:C_1206_3216Metric","","","","n.a.","","Supplier part not selected"
"MPPT","C33, C35, C37, C39","4","22uF","Capacitor_SMD:C_1206_3216Metric","","","","n.a.","","Supplier part not selected"
"MPPT","C40","1","100pF","Capacitor_SMD:C_0603_1608Metric","","","","n.a.","","Supplier part not selected"
"MPPT","D1, D2, D5","3","1N4148W","Diode_SMD:D_SOD-123","","","","n.a.","","Supplier part not selected"
"MPPT","D3","1","SS14","Diode_SMD:D_SMA","","","","n.a.","","Supplier part not selected"
"MPPT","D4","1","SMBJ24A_C123819","lcsc_footprints:C123819_SMB_L4_6-W3_6-LS5_3-RD","C123819","https://www.lcsc.com/product-detail/C123819.html","0.0593","0.0593","2026-11-19","SMBJ24A; unit price at 10+ pieces."
"MPPT","F2","1","3557-2","lcsc_footprints:C352820_FUSE-TH_4P-L19_8-W6_7_3557-2","C352820","https://www.lcsc.com/product-detail/C352820.html","1.4802","1.4802","2026-11-19","3557-2; unit price at 1+ pieces."
"MPPT","J4","1","Conn_01x05","Connector_PinHeader_2.54mm:PinHeader_1x05_P2.54mm_Vertical","","","","n.a.","","Supplier part not selected"
"MPPT","L1","1","CPEX3222L-470MC-RS","lcsc_footprints:C53145486_IND-TH_L32_2-W22_2_CPEX3222L","C53145486","https://www.lcsc.com/product-detail/C53145486.html","5.0594","5.0594","2026-11-19","CPEX3222L-470MC-RS; unit price at 1+ pieces."
"MPPT","L2","1","2.2uH","Inductor_SMD:L_Bourns-SRN4018","","","","n.a.","","Supplier part not selected"
"MPPT","L3","1","SRN8040TA","lcsc_footprints:C2044906_IND-SMD_L8_0-W8_0","C2044906","https://www.lcsc.com/product-detail/C2044906.html","0.7615","0.7615","2026-11-19","SRN8040TA-100M; unit price at 1+ pieces."
"MPPT","Q2, Q8, Q9","3","BSS83P","Package_TO_SOT_SMD:SOT-23","","","","n.a.","","Supplier part not selected"
"MPPT","Q3, Q4, Q5","3","PSMN5R2-60YL","Package_TO_SOT_SMD:LFPAK56","","","","n.a.","","Supplier part not selected"
"MPPT","Q6, Q7","2","MMBT3904","Package_TO_SOT_SMD:SOT-23","","","","n.a.","","Supplier part not selected"
"MPPT","Q10","1","BSC084P03NS3 G","lcsc_footprints:C534379_TDSON-8_L5_2-W5_9-P1_27-LS6_0-BL-EP","C672354","https://www.lcsc.com/product-detail/C672354.html","1.1136","1.1136","2026-11-19","BSC084P03NS3GATMA1; unit price at 1+ pieces."
"MPPT","R1, R17, R18, R25","4","10k","Resistor_SMD:R_0603_1608Metric","","","","n.a.","","Supplier part not selected"
"MPPT","R2, R24","2","24.9k","Resistor_SMD:R_0603_1608Metric","","","","n.a.","","Supplier part not selected"
"MPPT","R3, R4, R10, R21, R22, R23, R30","7","100k","Resistor_SMD:R_0603_1608Metric","","","","n.a.","","Supplier part not selected"
"MPPT","R5, R11","2","5.6k","Resistor_SMD:R_0603_1608Metric","","","","n.a.","","Supplier part not selected"
"MPPT","R6","1","1M","Resistor_SMD:R_0603_1608Metric","","","","n.a.","","Supplier part not selected"
"MPPT","R7, R9, R27, R29","4","470","Resistor_SMD:R_0603_1608Metric","","","","n.a.","","Supplier part not selected"
"MPPT","R8, R13","2","4R7","Resistor_SMD:R_0603_1608Metric","","","","n.a.","","Supplier part not selected"
"MPPT","R12","1","4R7","Resistor_SMD:R_0805_2012Metric","","","","n.a.","","Supplier part not selected"
"MPPT","R14, R19","2","3mR","lcsc_footprints:C840615_R2512","C840615","https://www.lcsc.com/product-detail/C840615.html","0.4295","0.859","2026-11-19","CRE2512-FZ-R001E-3; unit price at 1+ pieces. Code in footprint; verify part match"
"MPPT","R15, R26, R28, R31","4","2.2k","Resistor_SMD:R_0603_1608Metric","","","","n.a.","","Supplier part not selected"
"MPPT","R16","1","2R2","Resistor_SMD:R_0603_1608Metric","","","","n.a.","","Supplier part not selected"
"MPPT","R20","1","100","Resistor_SMD:R_0603_1608Metric","","","","n.a.","","Supplier part not selected"
"MPPT","RJ1","1","HX-RJ45 90 5631-1X1 8P8C S","lcsc_footprints:C25168872_RJ45-TH_HX-RJ45-90","C25168872","https://www.lcsc.com/product-detail/C25168872.html","0.143","0.143","2026-11-19","HX-RJ45 90 5631-1x1 8P8C S; unit price at 5+ pieces."
"MPPT","TH1","1","10K NTC","Resistor_THT:R_Axial_DIN0204_L3.6mm_D1.6mm_P5.08mm_Horizontal","","","","n.a.","","Supplier part not selected"
"MPPT","TP1","1","PWM_HS_TP","TestPoint:TestPoint_Pad_D1.0mm","","","","n.a.","","Supplier part not selected"
"MPPT","TP2","1","PWM_LS_TP","TestPoint:TestPoint_Pad_D1.0mm","","","","n.a.","","Supplier part not selected"
"MPPT","TP3","1","REF_TP","TestPoint:TestPoint_Pad_D1.0mm","","","","n.a.","","Supplier part not selected"
"MPPT","TP4","1","DCDC_CURRENT_TP","TestPoint:TestPoint_Pad_D1.0mm","","","","n.a.","","Supplier part not selected"
"MPPT","TP5","1","LOAD_CURRENT_TP","TestPoint:TestPoint_Pad_D1.0mm","","","","n.a.","","Supplier part not selected"
"MPPT","TP6","1","12VTP","TestPoint:TestPoint_Pad_D1.0mm","","","","n.a.","","Supplier part not selected"
"MPPT","TP7","1","5V_TP","TestPoint:TestPoint_Pad_D1.0mm","","","","n.a.","","Supplier part not selected"
"MPPT","TP8","1","3.3V_TP","TestPoint:TestPoint_Pad_D1.0mm","","","","n.a.","","Supplier part not selected"
"MPPT","U1, U5, U6","3","KF135T-10.16-2P","lcsc_footprints:C475108_CONN-TH_P10_16_KF135T-10_16-2P","C475108","https://www.lcsc.com/product-detail/C475108.html","0.5699","1.7096999999999998","2026-11-19","KF135T-10.16-2P; unit price at 1+ pieces."
"MPPT","U2","1","INA2181A","lcsc_footprints:C1848164_VSSOP-10_L3_0-W3_0-P0_50-LS4_9-BL","C1848164","https://www.lcsc.com/product-detail/C1848164.html","0.5701","0.5701","2026-11-19","INA2181A1IDGSR; unit price at 1+ pieces."
"MPPT","U3","1","LM5109BMA","Package_SO:SOIC-8_3.9x4.9mm_P1.27mm","C1549317","https://www.lcsc.com/product-detail/C1549317.html","1.0736","1.0736","2026-11-19","LM5109BMA/NOPB; unit price at 1+ pieces. Catalog candidate; verify ordering suffix"
"MPPT","U4","1","XT30AW-M.G.Y","lcsc_footprints:C19268026_CONN-TH_XT30AW-M_G_Y","C19268026","https://www.lcsc.com/product-detail/C19268026.html","0.4097","0.4097","2026-11-19","XT30AW-M.G.Y; unit price at 1+ pieces."
"MPPT","U7","1","STM32L072CZTx","Package_QFP:LQFP-48_7x7mm_P0.5mm","C1337587","https://www.lcsc.com/product-detail/C1337587.html","5.9667","5.9667","2026-11-19","STM32L072CZT6; unit price at 1+ pieces. Catalog candidate; verify ordering suffix"
"MPPT","U8","1","LMR33630","Package_SO:Texas_HSOP-8-1EP_3.9x4.9mm_P1.27mm_ThermalVias","C2866787","https://www.lcsc.com/product-detail/C2866787.html","1.0284","1.0284","2026-11-19","LMR33630ADDA; unit price at 1+ pieces. Catalog candidate; verify ordering suffix"
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
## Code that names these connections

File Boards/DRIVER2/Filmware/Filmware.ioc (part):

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Mcu.Name=STM32F429Z(E-G)Tx
Mcu.Package=LQFP144
Mcu.UserName=STM32F429ZGTx
PA0/WKUP.Signal=ADCx_IN0
PA13.Mode=Serial_Wire
PA13.Signal=SYS_JTMS-SWDIO
PA14.Mode=Serial_Wire
PA14.Signal=SYS_JTCK-SWCLK
PB10.Mode=I2C
PB10.Signal=I2C2_SCL
PB11.Mode=I2C
PB11.Signal=I2C2_SDA
PB6.Mode=I2C
PB6.Signal=I2C1_SCL
PB7.Mode=I2C
PB7.Signal=I2C1_SDA
PD4.GPIOParameters=GPIO_Label
PD4.GPIO_Label=RS485_5_DIR
PD4.Signal=GPIO_Output
PD5.Mode=Asynchronous
PD5.Signal=USART2_TX
PD6.Mode=Asynchronous
PD6.Signal=USART2_RX
PD9.GPIOParameters=GPIO_Label
PD9.GPIO_Label=SENS3_IN
PD9.Signal=GPIO_Input
PE3.GPIOParameters=PinState,GPIO_Label
PE3.GPIO_Label=FRAM_WP
PE3.PinState=GPIO_PIN_SET
PE3.Signal=GPIO_Output
PE4.GPIOParameters=GPIO_Label
PE4.GPIO_Label=WD_ENABLE
PE4.Signal=GPIO_Output
PE5.GPIOParameters=GPIO_Label
PE5.GPIO_Label=WD_KICK
PE5.Signal=GPIO_Output
PE6.GPIOParameters=GPIO_Label
PE6.GPIO_Label=MCU_ARM
PE6.Signal=GPIO_Output
PE7.GPIOParameters=GPIO_Label
PE7.GPIO_Label=PWR_FAULT_N
PE7.Signal=GPIO_Input
PE8.GPIOParameters=GPIO_Label
PE8.GPIO_Label=PWR_GOOD
PE8.Signal=GPIO_Input
PF11.GPIOParameters=GPIO_Label
PF11.GPIO_Label=AUX1_CMD
PF11.Signal=GPIO_Output
PF12.GPIOParameters=GPIO_Label
PF12.GPIO_Label=AUX2_CMD
PF12.Signal=GPIO_Output
PF13.GPIOParameters=GPIO_Label
PF13.GPIO_Label=AUX3_CMD
PF13.Signal=GPIO_Output
PF14.GPIOParameters=GPIO_Label
PF14.GPIO_Label=BTN_UP
PF14.Signal=GPIO_Input
PF15.GPIOParameters=GPIO_Label
PF15.GPIO_Label=BTN_DOWN
PF15.Signal=GPIO_Input
PF6.GPIOParameters=GPIO_Label
PF6.GPIO_Label=PUMP1_CMD
PF6.Signal=GPIO_Output
PF7.GPIOParameters=GPIO_Label
PF7.GPIO_Label=PUMP2_CMD
PF7.Signal=GPIO_Output
PF8.GPIOParameters=GPIO_Label
PF8.GPIO_Label=PUMP3_CMD
PF8.Signal=GPIO_Output
PF9.GPIOParameters=GPIO_Label
PF9.GPIO_Label=PUMP4_CMD
PF9.Signal=GPIO_Output
PG0.GPIOParameters=GPIO_Label
PG0.GPIO_Label=BTN_OK
PG0.Signal=GPIO_Input
RCC.HSE_VALUE=25000000
RCC.SYSCLKFreq_VALUE=16000000
board=custom

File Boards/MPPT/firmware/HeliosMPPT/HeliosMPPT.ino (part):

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    const uint32_t started=micros();
    const uint16_t ref=readAdc(AVREF);
    const float supply=ref?__LL_ADC_CALC_VREFANALOG_VOLTAGE(ref,LL_ADC_RESOLUTION_12B)/1000.0f*cfg::vddaCalibration:NAN;
    const uint16_t bat=readAdc(PA0),pv=readAdc(PA1),conv=readAdc(PA6),load=readAdc(PA5),ntc=readAdc(PA7);
    helios::Sample s;s.at=nowMs;
    s.battery=adcVolts(bat,supply)*cfg::voltageRatio*cfg::batteryVoltageCalibration;
    s.panel=adcVolts(pv,supply)*cfg::voltageRatio*cfg::panelVoltageCalibration;
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    }
    const uint32_t requested=command;command=0;
    if(requested==1&&configured)controller.start();
    if(requested==2){controller.stop();stage.stop();digitalWrite(PC13,LOW);}
    if(requested==3) {
        stage.stop();controller.clear();heartbeatFault=false;
        lastHealthyMs=heartbeatMs;
    }
}
void setup() {
    outputLow(PB0);outputLow(PB1);outputLow(PC13);
    outputLow(PB10);outputLow(PC14);outputLow(PA8);
    pinMode(PC15,INPUT);
    analogReadResolution(12);analogWriteResolution(12);
    analogWrite(PA4,2048); // INA2181A1 reference; PA4 is a hardware DAC pin.
    digitalWrite(PC14,HIGH); // PV DIVIDER enable, not power-stage enable.
    digitalWrite(PB10,HIGH); // 5 V buck enable.
    delay(50);
    stage.begin();
    telemetry.timerTop=stage.top();telemetry.deadTimeTicks=stage.gap();
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    if(uint32_t(nowUs-lastSampleUs)>=1000) {
        lastSampleUs=nowUs;
        auto s=measure(nowMs);
        const bool good=digitalRead(PC15)==LOW; // Q8 inverts U8 power-good.
        telemetry.powerGood=good;
        if(good) {lastPgFailMs=nowMs;if(!pgWasGood)pgGoodAtMs=nowMs;}
        else {pgGoodAtMs=nowMs;if(pgWasGood)lastPgFailMs=nowMs;}
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            lastHealthyMs=heartbeatMs;
            stage.apply(result.duty,synchronous);
        }
        digitalWrite(PC13,result.load&&allowed?HIGH:LOW);
        if(!irq)__enable_irq();
        telemetry.state=uint8_t(result.state);telemetry.fault=uint8_t(result.fault);
        telemetry.outputW=result.power;telemetry.batteryA=result.batteryCurrent;
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        // Both safety mechanisms are fed only after returning from a complete sample/control pass.
        IWDG->KR=0xAAAA;
    }
    // PB10 remains enabled: switching this rail off would return the LDO to battery input.
    if(cfg::uartTelemetry&&helios::elapsed(nowMs,lastReportMs,1000)) {
        lastReportMs=nowMs;
        console.print("state=");console.print(telemetry.state);
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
